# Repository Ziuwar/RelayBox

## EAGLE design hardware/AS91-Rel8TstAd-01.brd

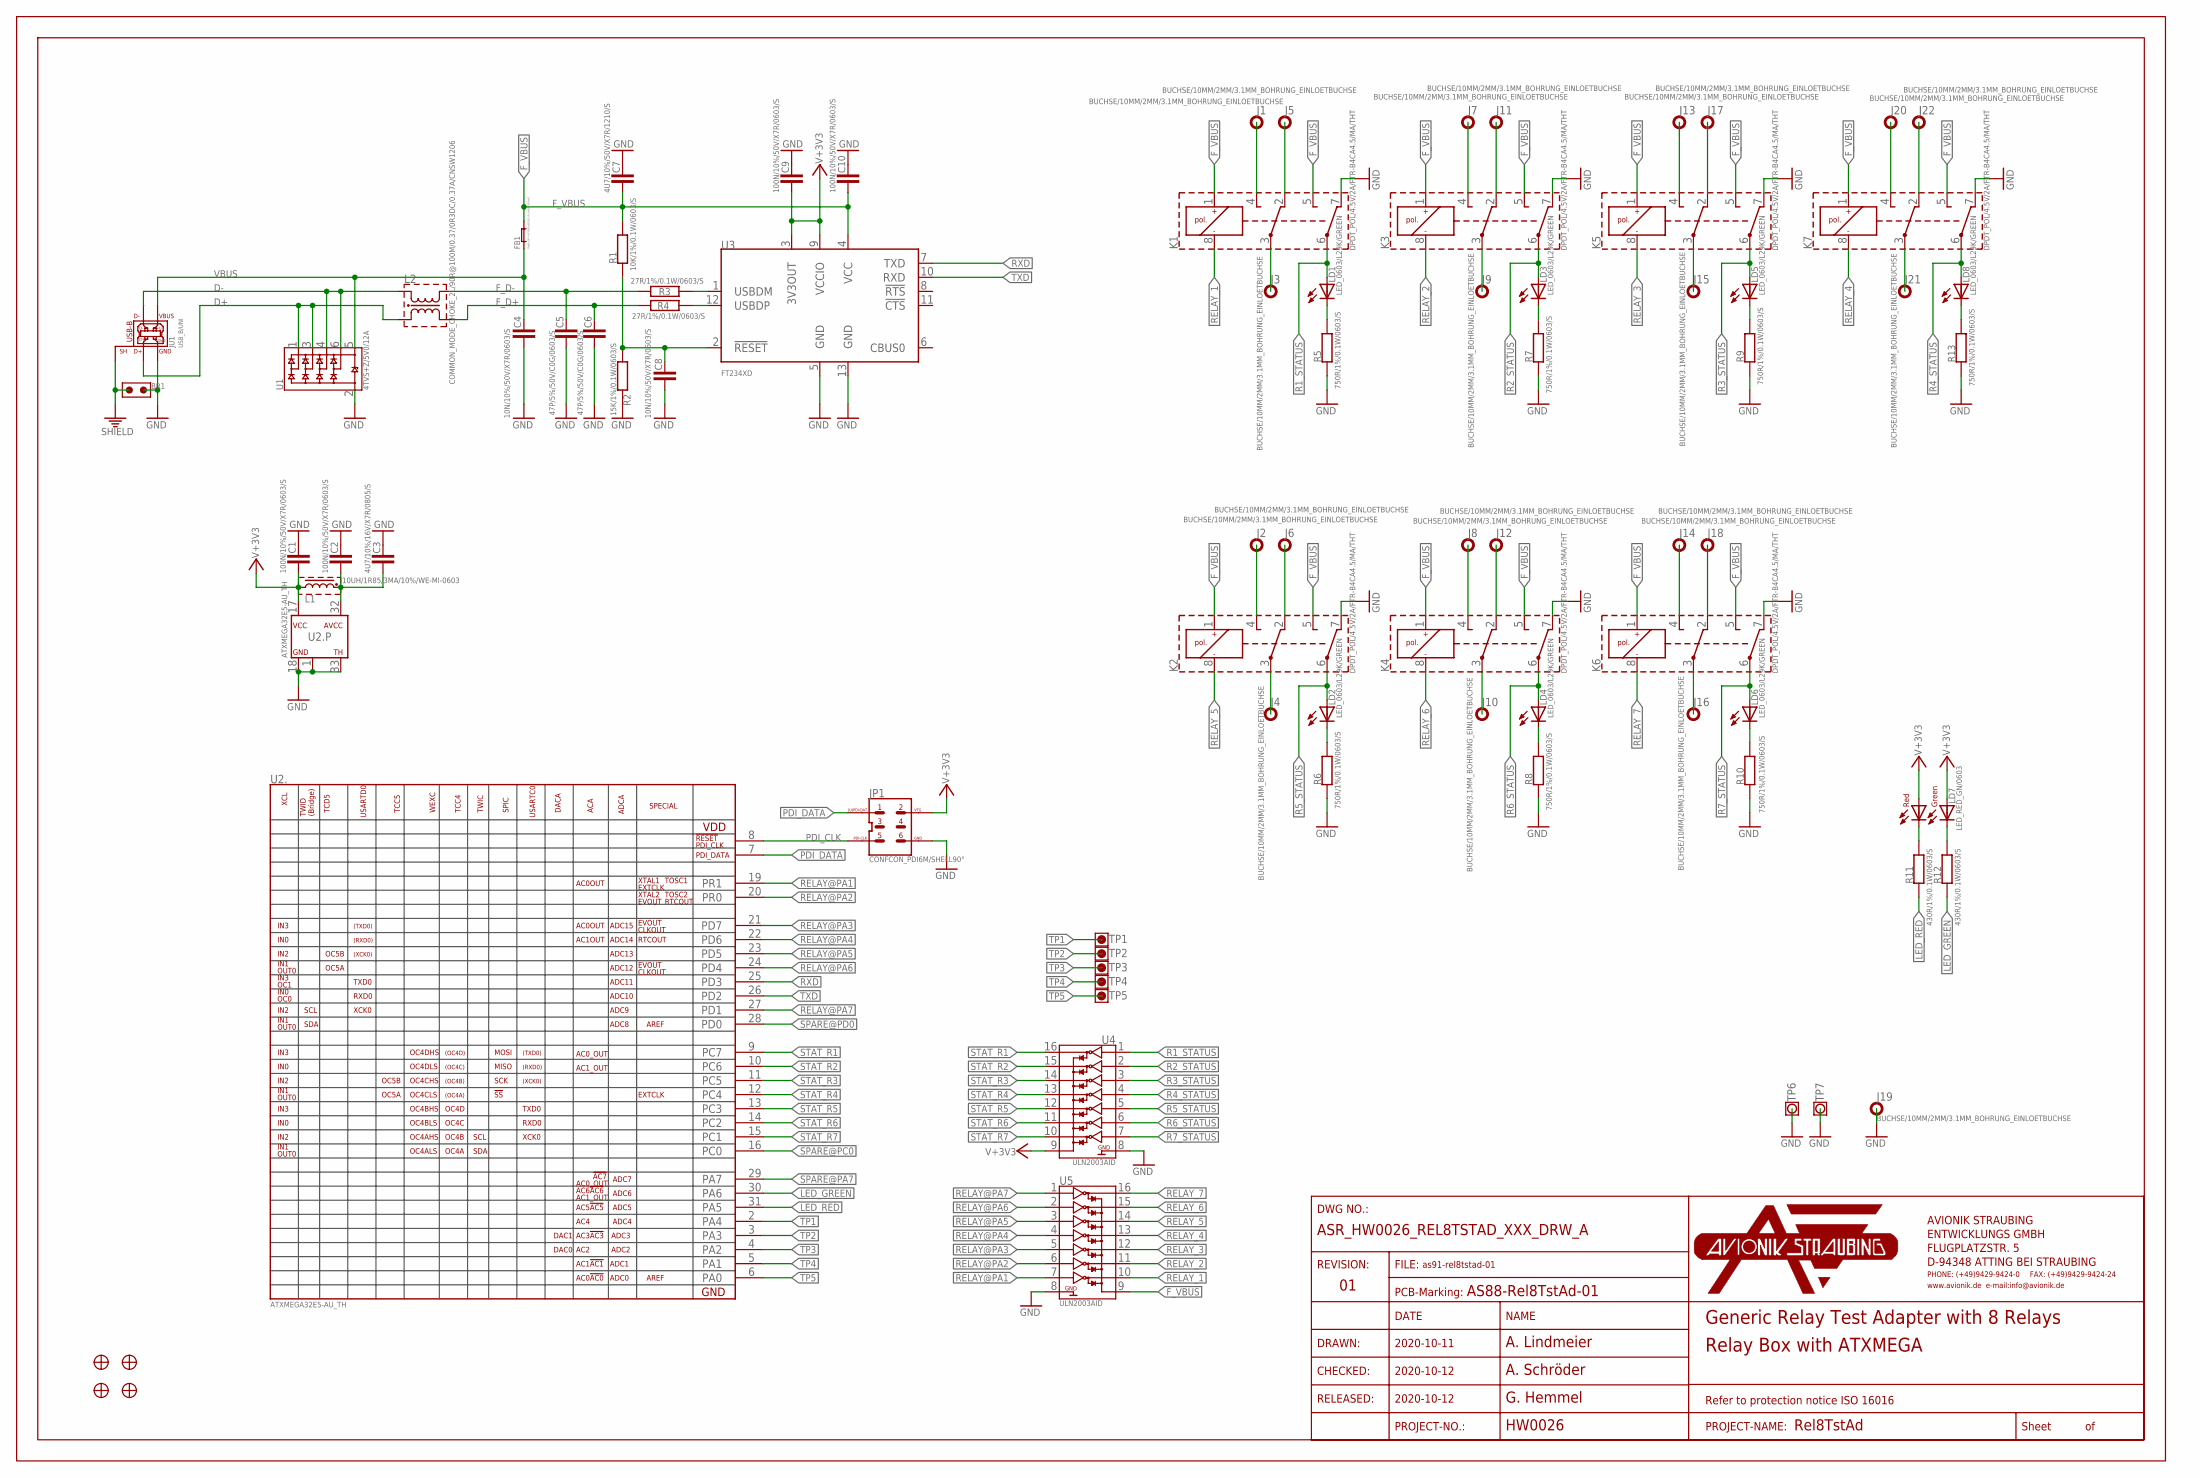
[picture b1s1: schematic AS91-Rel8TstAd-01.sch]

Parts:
BR1: BRIDGE_OPEN/SOLDER; SOLDER_OPEN
C1, C2, C9, C10: 100N/10%/50V/X7R/0603/S; C0603_STD
C3: 4U7/10%/16V/X7R/0805/S; C0805_STD
C4, C8: 10N/10%/50V/X7R/0603/S; C0603_STD
C5, C6: 47P/5%/50V/C0G/0603/S; C0603_STD
C7: 4U7/10%/50V/X7R/1210/S; C1210_STD
DRAWING_FRAME1: DIN_A3LOC_PCBMARK_ASR/TOP/STOP/0.8; FRAME_REVISION_TOP_STOP_0.8
FB1: FB/WE-CBF/742792620/DC0R15/0.5A/WE/CBF0603; WE_CBF_0603
J1, J2, J3, J4, J5, J6, J7, J8, J9, J10, J11, J12, J13, J14, J15, J16, J17, J18, J19, J20, J21, J22: BUCHSE/10MM/2MM/3.1MM_BOHRUNG_EINLOETBUCHSE; BUCHSE2MM_PCB3.1MMDRILL
JP1: CONFCON_PDI6M/SHELL90°; PH2X3_WSL_SHELL_90°
JU1: USB_B/UNI; USB-B-BUCHSE-LP
K1, K2, K3, K4, K5, K6, K7: DPDT_POL/4.5V/2A/FTR-B4CA4.5/MA/THT; FTR-B4
L1: 10UH/1R85/3MA/10%/WE-MI-0603; WE-MI_0603
L2: COMMON_MODE_CHOKE_2L/90R@100M/0.37/0R3DC/0.37A/CN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; WUERTH_CNSW_1206
LD1, LD2, LD3, LD4, LD5, LD6, LD8: LED_0603/L29K/GREEN; CHIPLED0603SMALL
LD7: LED_RED_GN/0603; DUOLED_0603
PCB1: TEKO_MOD_P2; BOARD_TEKO_MOD_P2_UP
R1: 10K/1%/0.1W/0603/S; R0603_STD
R2: 15K/1%/0.1W/0603/S; R0603_STD
R3, R4: 27R/1%/0.1W/0603/S; R0603_STD
R5, R6, R7, R8, R9, R10, R13: 750R/1%/0.1W/0603/S; R0603_STD
R11, R12: 430R/1%/0.1W/0603/S; R0603_STD
TP1, TP2, TP3, TP4, TP5: TESTPAD_ROUND/1.0MM; TP_ROUND_SMD_1MM
TP6, TP7: TESTPOINT_1/OCT_0.8; TP_OCT_0.8_DRILL
U1: 4TVS+Z/5V0/12A; SOT23-6L
U2: ATXMEGA32E5-AU_TH; TQFP32A_THGND
U3: FT234XD
U4, U5: ULN2003AID; SO16

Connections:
D+: JU1.3 (D+), L2.1 (L2_A), U1.1 (IO1), U1.3 (IO2)
D-: JU1.2 (D-), L2.4 (L1_A), U1.4 (IO3), U1.6 (IO4)
F_D+: C6.1, L2.2 (L2_B), R4.1
F_D-: C5.1, L2.3 (L1_B), R3.1
F_VBUS: C7.2, C10.2, FB1.2, K1.1 (K+), K1.5 (NO2), K2.1 (K+), K2.5 (NO2), K3.1 (K+), K3.5 (NO2), K4.1 (K+), K4.5 (NO2), K5.1 (K+), K5.5 (NO2), K6.1 (K+), K6.5 (NO2), K7.1 (K+), K7.5 (NO2), R1.2, U3.4 (VCC), U5.9 (CFW)
GND: BR1.CENT, C1.1, C2.1, C3.1, C4.2, C5.2, C6.2, C7.1, C8.2, C9.1, C10.1, J19.1, JP1.6 (GND), JU1.4 (GND), K1.7 (NC2), K2.7 (NC2), K3.7 (NC2), K4.7 (NC2), K5.7 (NC2), K6.7 (NC2), K7.7 (NC2), R2.1, R5.1, R6.1, R7.1, R8.1, R9.1, R10.1, R13.1, TP6.A, TP7.A, U1.2 (GND), U2.1 (GND), U2.18 (GND), U2.33 (GND), U3.5 (GND), U3.13 (GND), U4.8 (GND), U5.8 (GND)
LED_GREEN: R12.1, U2.30 (PA6)
LED_RED: R11.1, U2.31 (PA5)
unnamed: J7.1, K3.4 (NO1)
unnamed: J11.1, K3.2 (NC1)
unnamed: J1.1, K1.4 (NO1)
unnamed: J9.1, K3.3 (COM1)
unnamed: J13.1, K5.4 (NO1)
unnamed: J17.1, K5.2 (NC1)
unnamed: J15.1, K5.3 (COM1)
unnamed: J20.1, K7.4 (NO1)
unnamed: LD7.3 (C_GN), R12.2
unnamed: R3.2, U3.1 (USBDM)
unnamed: R4.2, U3.12 (USBDP)
unnamed: J2.1, K2.4 (NO1)
unnamed: J5.1, K1.2 (NC1)
unnamed: C8.1, R1.1, R2.2, U3.2 (!RESET)
unnamed: LD7.4 (C_RED), R11.2
unnamed: J3.1, K1.3 (COM1)
unnamed: J22.1, K7.2 (NC1)
unnamed: J21.1, K7.3 (COM1)
unnamed: J6.1, K2.2 (NC1)
unnamed: J4.1, K2.3 (COM1)
unnamed: J8.1, K4.4 (NO1)
unnamed: J12.1, K4.2 (NC1)
unnamed: J10.1, K4.3 (COM1)
unnamed: J14.1, K6.4 (NO1)
unnamed: J18.1, K6.2 (NC1)
unnamed: J16.1, K6.3 (COM1)
unnamed: LD1.C, R5.2
unnamed: LD3.C, R7.2
unnamed: LD5.C, R9.2
unnamed: LD8.C, R13.2
unnamed: LD6.C, R10.2
unnamed: LD4.C, R8.2
unnamed: LD2.C, R6.2
unnamed: C2.2, C3.2, L1.1, U2.32 (AVCC)
PDI_CLK: JP1.5 (PDI_CLK), U2.8 (PDI_CLK/!RESET)
PDI_DATA: JP1.1 (PDI_DATA), U2.7 (PDI_DATA)
R1_STATUS: K1.6 (COM2), LD1.A, U4.1 (IN1)
R2_STATUS: K3.6 (COM2), LD3.A, U4.2 (IN2)
R3_STATUS: K5.6 (COM2), LD5.A, U4.3 (IN3)
R4_STATUS: K7.6 (COM2), LD8.A, U4.4 (IN4)
R5_STATUS: K2.6 (COM2), LD2.A, U4.5 (IN5)
R6_STATUS: K4.6 (COM2), LD4.A, U4.6 (IN6)
R7_STATUS: K6.6 (COM2), LD6.A, U4.7 (IN7)
RELAY@PA1: U2.19 (PR1), U5.7 (IN7)
RELAY@PA2: U2.20 (PR0), U5.6 (IN6)
RELAY@PA3: U2.21 (PD7), U5.5 (IN5)
RELAY@PA4: U2.22 (PD6), U5.4 (IN4)
RELAY@PA5: U2.23 (PD5), U5.3 (IN3)
RELAY@PA6: U2.24 (PD4), U5.2 (IN2)
RELAY@PA7: U2.27 (PD1), U5.1 (IN1)
RELAY_1: K1.8 (K-), U5.10 (OUT7)
RELAY_2: K3.8 (K-), U5.11 (OUT6)
RELAY_3: K5.8 (K-), U5.12 (OUT5)
RELAY_4: K7.8 (K-), U5.13 (OUT4)
RELAY_5: K2.8 (K-), U5.14 (OUT3)
RELAY_6: K4.8 (K-), U5.15 (OUT2)
RELAY_7: K6.8 (K-), U5.16 (OUT1)
RXD: U2.25 (PD3), U3.7 (TXD)
SHIELD: BR1.A, JU1.SH1, JU1.SH2 (SH1)
SPARE@PA7: U2.29 (PA7)
SPARE@PC0: U2.16 (PC0)
SPARE@PD0: U2.28 (PD0)
STAT_R1: U2.9 (PC7), U4.16 (OUT1)
STAT_R2: U2.10 (PC6), U4.15 (OUT2)
STAT_R3: U2.11 (PC5), U4.14 (OUT3)
STAT_R4: U2.12 (PC4), U4.13 (OUT4)
STAT_R5: U2.13 (PC3), U4.12 (OUT5)
STAT_R6: U2.14 (PC2), U4.11 (OUT6)
STAT_R7: U2.15 (PC1), U4.10 (OUT7)
TP1: TP1.1, U2.2 (PA4)
TP2: TP2.1, U2.3 (PA3)
TP3: TP3.1, U2.4 (PA2)
TP4: TP4.1, U2.5 (PA1)
TP5: TP5.1, U2.6 (PA0)
TXD: U2.26 (PD2), U3.10 (RXD)
V+3V3: C1.2, C9.2, JP1.2 (VTG), L1.2, LD7.1 (A_GN), LD7.2 (A_RED), U2.17 (VCC), U3.3 (3V3OUT), U3.9 (VCCIO), U4.9 (CFW)
VBUS: C4.1, FB1.1, JU1.1 (VBUS), U1.5 (VDD)

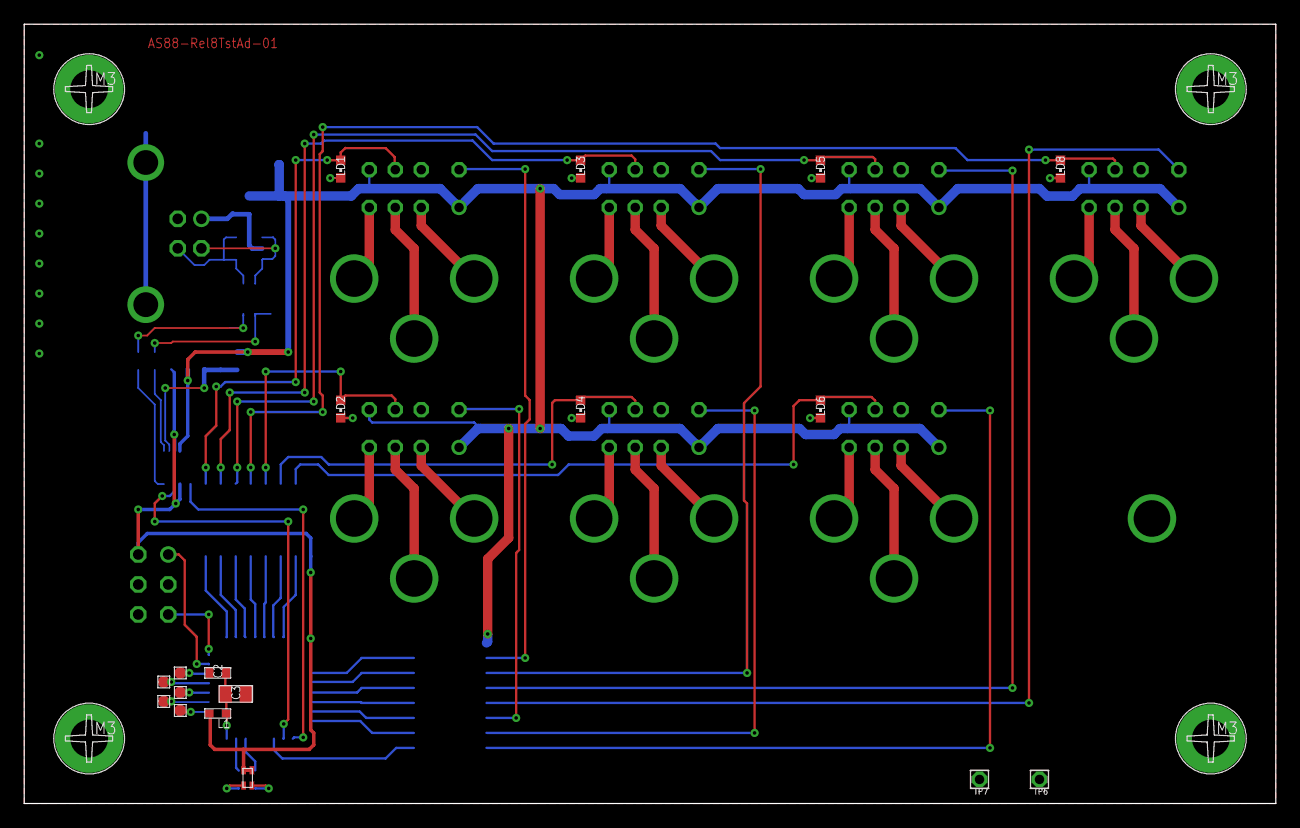
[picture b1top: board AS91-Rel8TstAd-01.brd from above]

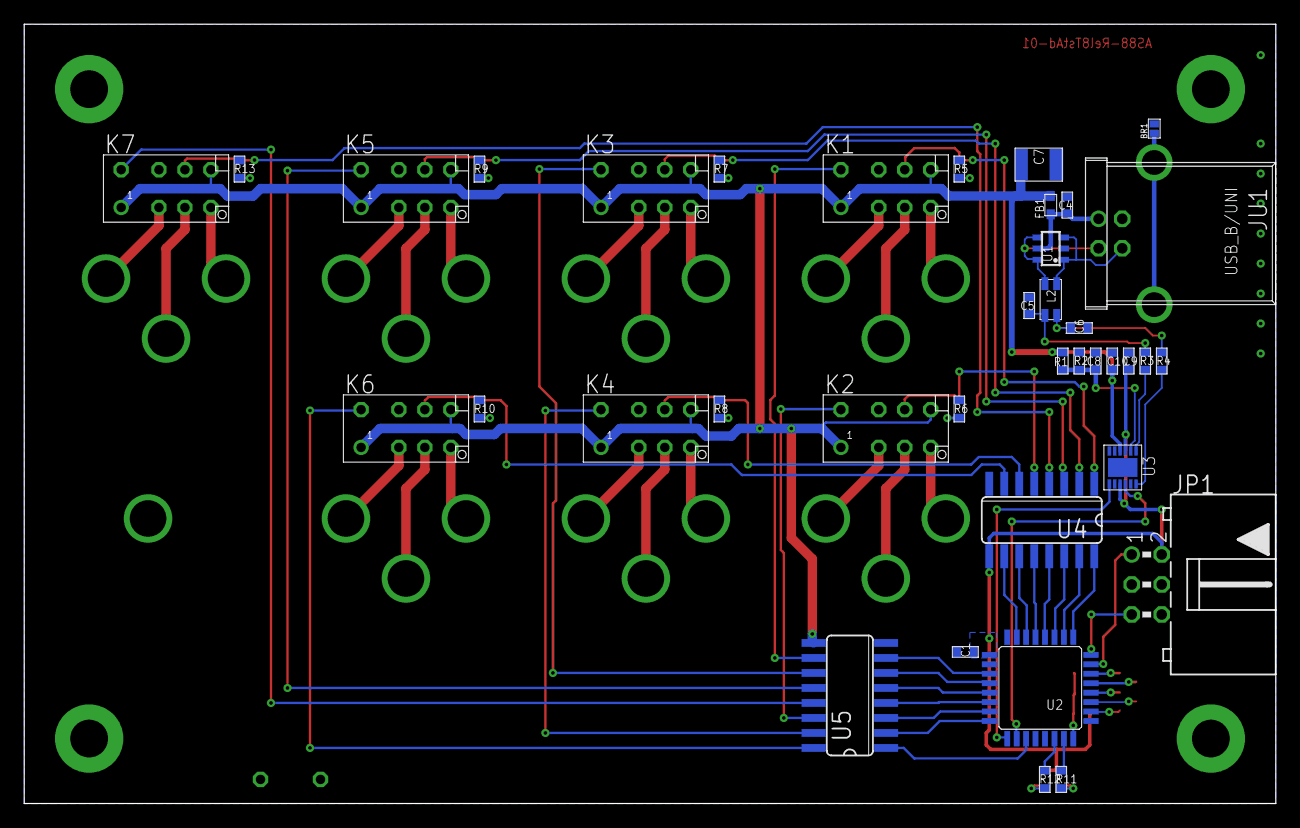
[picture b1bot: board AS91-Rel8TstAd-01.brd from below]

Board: 2 copper layers, 106.0 x 66.0 mm, 80 parts (38 on the bottom side), 82 nets.

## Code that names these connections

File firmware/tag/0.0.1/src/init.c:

#include "init.h"

#include <avr/io.h>
#include <avr/interrupt.h>

#define F_CPU 3333333U // The CPU speed -> 20 MHz / 6 = 3.33 MHz
#define USART0_BAUD_RATE(BAUD_RATE) ((float) (F_CPU * 64U / (16U * (float)BAUD_RATE)) + 0.5f) // Calculates the register setting for the given CPU speed and baud rate

#ifdef __cplusplus
extern "C" {
#endif

// Initialization of the interrupts
void interrupt_init(void)
{
    USART0.CTRLA |= USART_RXCIE_bm;		 	// Enables the receive interrupt complete vector for UART0
    RTC.INTCTRL  |= RTC_CMP_bm;				// Enables the RTC compare interrupt
    sei();									// Enable global interrupts
}

// IO config
void port_config(void)
{
    // Outputs
    PORTA.DIR |= PIN1_bm;	// Relay_1
    PORTA.DIR |= PIN2_bm;	// Relay_2
    PORTA.DIR |= PIN3_bm;	// Relay_3
    PORTA.DIR |= PIN4_bm;	// Relay_4
    PORTA.DIR |= PIN5_bm;	// Relay_5
    PORTA.DIR |= PIN6_bm;	// Relay_6
    PORTA.DIR |= PIN7_bm;	// Relay_7

    PORTB.DIR |= PIN0_bm;	// LED LD1
    PORTB.PIN0CTRL |= 0x80;	// Invert bit
    PORTB.DIR |= PIN1_bm;	// LED LD2
    PORTB.PIN1CTRL |= 0x80; // Invert bit
}

// USART0 Initialization
void USART0_init(void)
{
    PORTB.DIR &= ~PIN3_bm; // UART RX -> Input
    PORTB.DIR |= PIN2_bm;  // UART TX -> Output

    USART0.BAUD = (uint16_t) USART0_BAUD_RATE(9600);	// Set the register to baud rate 9600 using the defined macro
    USART0.CTRLB |= USART_RXEN_bm | USART_TXEN_bm;			// Set the tx and rx enable to 1 (enabled)
}

// Timer RTC configuration
void RTC_config(void)
{
    RTC_CLKSEL	|= RTC_CLKSEL_INT1K_gc;		// Set clock source to OSCULP32K (1,024 kHz)
    while(!(RTC.STATUS == 0x00U)) { }		// Wait for the RTC to be ready for config
    RTC.CTRLA	|= RTC_PRESCALER_DIV1_gc;	// Set prescaler to DIV1, results in a timer with 1,024 ms
    RTC.CMP		|= 0x01E9U;					// Sets the compare to 489, resulting in 500,736 ms time slots
    while(!(RTC.STATUS == 0x00U)) { }		// Wait for the RTC to be ready for config
    RTC.CTRLA	|= 0x1U;					// Enable the RTC
}







#ifdef __cplusplus
}
#endif

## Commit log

2021-08-22 Add files via upload
    Added the latest version.
